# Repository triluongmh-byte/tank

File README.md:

# Pet Tank 🛞🤖

**English** · [Tiếng Việt](README.vi.md)

A 6-wheel armored-car-style tank cloned from **claude-pet**. A screen on the sloped front face shows the pet face and the status of Claude Code sessions. A turret carries two sonars mounted back to back for finding a path.

- **Body:** the `robot-tank` v1 case designed in cadsmith, already printed by the owner, plus the v5 board stack and glue-on/clip-on holders.
- **Board:** 62×60 mm two-layer carrier.
- **Control:** ESP32 DevKit + PCA9685 driving 7 servos: six 360° wheel servos and one SG90 turret servo.
- **Power:** two 18650 cells in parallel (1S) through a pack protector and two 5 V boost modules.

> **Status:** the design passed the team's board, firmware, case and integration checks. **Hardware is untested.** The firmware has not been flashed, the new holders have not been printed, and no board has been ordered. Module dimensions in the docs are **ASSUMPTIONS**: measure the real modules before printing or soldering.

## What's in the repo

| Folder | Contents |
|---|---|
| `design/` | KiCad project: schematic, PCB, libraries, component 3D models |
| `engineering/` | Power ([POWER_SYSTEM.md](engineering/POWER_SYSTEM.md)), stack wiring ([STACK_WIRING.md](engineering/STACK_WIRING.md)), assembly, bring-up, pinout, calculations |
| `parts.json`, `product.json`, `manufacturing.json` | BOM (LCSC part numbers), board description, fabrication settings |
| `case/` | CadQuery scripts for the holders ([build.py](case/build.py), `holders.py`, `stack.py`, `power_b.py`, `logic_b.py`). `case/ref/v1` and `case/ref/v5` hold the original STEP files of the printed robot-tank, unchanged |
| `firmware/` | ESP32 firmware (`firmware/tank/`), [wiring guide](firmware/WIRING.md), [host protocol](firmware/PROTOCOL.md), host-side tests (`firmware/tests/`), host bridge (`firmware/host/`) |
| `tools/` | Check and export scripts for each team (board, case, firmware) |
| `contract/` | The sealed team contract and release notes (the owner's words verbatim, plus how the lead interpreted them) |
| `prompts/`, `references/` | Original request, request history, reference images. STEP/STL files under `prompts/assets` are not committed; their hashes are in the `SHA256SUMS` files |

Not committed, because `./build.sh` regenerates them: STL/STEP/3MF, Gerbers, zips, renders, `build/`, `boards/`, `case/out/`, `case/print/`, firmware binaries. Datasheets are not committed either; their links are in `engineering/sources/manifest.json`.

Most docs inside the subfolders are written in Vietnamese.

## Build

```sh
./build.sh              # board -> case -> firmware
./build.sh firmware     # a single stage
./build.sh board case
```

Requirements (nothing is installed from the network):

- `KICAD_HARNESS_PYTHON` (Python with `kicadpy`) and `KICAD_CASE_PYTHON` (Python with CadQuery + `kicadpy`). Harness provides both.
- KiCad 9 `kicad-cli`. The script looks in `/Applications/KiCad/KiCad.app`, or set `KICAD_CLI`.
- Bambu Studio at `/Applications/BambuStudio.app`, used to slice `case/print/*.3mf`. No print job is ever sent.
- `arduino-cli` with core `esp32:esp32@2.0.14` already installed. If the core is outside the default location, point `ARDUINO_DIRECTORIES_DATA` at it (Harness keeps it in `~/.cache/autonomous-circuit/firmware/arduino`).

A build rewrites a few committed files: the board STEP hashes in `case/ref/board/SHA256SUMS`, `engineering/step-handoff.json` and `case/firmware-limits.json`. Seeing them change after a build is expected.

What each stage does:

- **board:** runs the official board checks (ERC/DRC, netlist, gate) and writes the manufacturing packet to `boards/`. Exports the populated board STEP to `build/board/main-contract.step` and hands it to the case (`case/ref/board/`, hashes recomputed).
- **case:** runs `case/build.py`, which writes STEP/STL to `case/out/`. Then runs the three case checks: printability and collisions, v5 against v1, and turret sweep. Then generates the print plates `case/print/production.3mf` + `test-only.3mf` and `case/overview.html`, and runs `kicadpy.case check-print` (printable surfaces, bed fit).
- **firmware:** runs the host tests, including mocks and ASan/UBSan, then compiles the ESP32 build to `build/firmware/esp32/tank.ino.bin`. **Nothing is flashed.**

When a requested stage reads another stage's output and that output is missing, `build.sh` runs that stage too. The case needs the board STEP. The firmware needs `case/reports/turret_yaw.json` for the turret limits.

## What the firmware does

- Keeps claude-pet's pet face and Claude Code session status, now on a 1.54" 240×240 ST7789 screen.
- Talks to a computer over USB (UART0, 115200).
- **Phone control**, modelled on the UI of the owner's crab-robot-v17g:
  - The tank starts its own open Wi-Fi network named `XeTang-XXXX`. The screen shows the network name, the address and a QR code.
  - Join that network and open `http://192.168.4.1/`. Many phones open the page on their own.
  - **Drive** page: an 8-direction pad. Hold a button to drive, release to stop. Three speeds: 0.4 / 0.65 / 1. Forward or reverse is blocked when the sonar facing that way sees an obstacle closer than 350 mm, or has no fresh reading (older than 250 ms). The light button shows "not connected" because the lights have no control pin yet.
  - **Assembly** page: set the centre, limits and direction for each wheel, centre the turret (limited to ±70°), then Save. Driving is refused until calibration is done.
  - **Wi-Fi** page (optional): join a home network. The password is stored in NVS.
  - Every stop source wins: releasing the button, no command for 500 ms, losing the phone connection, the STOP button, an I2C error, the watchdog.
  - The constants (500 ms, 5 s, 60 % pulse at speed 1) are **untested** on the real tank and a real phone.
- The board adds a logic boost module, `M_LOGIC` (Pololu U3V16F5), that powers the DevKit over USB from the battery. The tank can run without a computer attached.
- Drives the six wheels (PCA CH0–5) with per-wheel calibration, and the turret (CH6).
- A stop-and-go path-finding mode using the two HC-SR04P sonars. `AUTO SCAN` stays locked until the real turret angles are measured on the tank.
- Always boots stopped. Losing the link, a missed heartbeat, or the STOP button (GPIO27) cuts servo power.

GPIO map: see [firmware/README.md](firmware/README.md) and [engineering/esp32-pinmap.json](engineering/esp32-pinmap.json).

## Case: what to print and how to assemble

See [case/README.md](case/README.md). In short:

- **Do not reprint** the robot-tank v1 parts that are already printed: chassis, hull, lid, turret, light bracket, six arms, six wheels.
- Print the new glue-on/clip-on holders and the **v5 stack**: base, PCA9685 + fan tier, ESP32 tier, and a cap with a turret-servo pocket and a 45° face for the screen.
- **Layout B** is the chosen layout: the lid is removed and the stack stands on a bridge plate above the two cells. Total height is **214.8 mm**, against 118.3 mm for v1. Only layout B fits the 62×60 carrier with all the modules.
- Print the **TEST ONLY** plate first and try it with the real modules before printing the production plates.

## Things you may need to fix by hand

The testers recorded the points below. Items 1–8 come from run `r006` and may be partly fixed. Items 9–11 come from the latest run, `r007`. Neither run produced a `lead-document-findings.json`. None of these have been measured on hardware.

1. **The servo boost converters are near their limit.** The estimated peak current drawn from the battery is ~8.9 A, above the 8 A typical rating of the Pololu U3V70F5. Measure the real current with all six wheels stalled or starting, and consider limiting speed or splitting the load.
2. **The power docs still contain old text.** Some lines in `product.json`, `engineering/POWER_SYSTEM.md` and `parts.json` still describe the old power chain (TPS61287, LILYGO, 100×70 carrier, 12 AWG / 30 A wiring). The current design uses two Pololu U3V70F5 modules, an ESP32 DevKit and a 62×60 carrier. The main battery lead needs connectors rated ≥15 A to match the `F_PACK` fuse.
3. **ACT_EN while the ESP32 boots.** The second boost module's ENABLE pin is tied to ACT_EN through a Dupont lead and pulled up to VIN (≤4.2 V) through 100 kΩ. Check on the bench that ACT_EN stays low while the ESP32 boots and resets, so the servos don't twitch.
4. **The 2×6 header orientation in `firmware/WIRING.md`** does not match the new 62×60 layout. Use [engineering/pinout.md](engineering/pinout.md) when crimping the `J_CTRL` / `J_PCA` leads.
5. **The unfused battery lead is ~35 mm long**, over the ≤25 mm limit. Move the `fuse_holder_pack` holder closer to the cells, or fit `F_PACK` inside the battery pack.
6. **There is no place for the charger on the tank.** To charge, unplug the RUN connector and charge on the bench.
7. **Module dimensions are assumed:** ESP32 51.5×28.3, PCA9685 62.2×25.4, fan 30×30×10, screen 32×38×4 mm. Measure the real parts and print the TEST ONLY coupons first.
8. **Layout B makes the tank almost twice as tall** and drops the lid. Keeping the v1 lid needs a redesign by the team.
9. **The power diagrams don't show `M_LOGIC` yet.** Parts of `engineering/POWER_SYSTEM.md` still say the DevKit takes 5 V from its own USB supply, and one line still mentions the LILYGO. `case/logic_b.py` and the firmware integration report still refer to the old "optional chain". The bring-up order in `firmware/WIRING.md` (logic first, then islands A/B) does not match the diagram, where all three boost modules are wired in parallel at the RUN lead.
10. **Where the DevKit sits:** the `M_LOGIC` wire route says the DevKit is on "tier 3", while `STACK_WIRING.md` and `parts.json` put it on tier 2. Tier 2 is correct.
11. **Power the DevKit through its USB port only.** Do not also feed its VIN pin in parallel with USB.

## Safety

A 1S Li-ion pack delivers high current. Fit the protector and fuses described in [engineering/POWER_SYSTEM.md](engineering/POWER_SYSTEM.md). Never connect the outputs of the two boost modules in parallel. Never power the servos from the DevKit's 5V pin or from a computer's USB port.

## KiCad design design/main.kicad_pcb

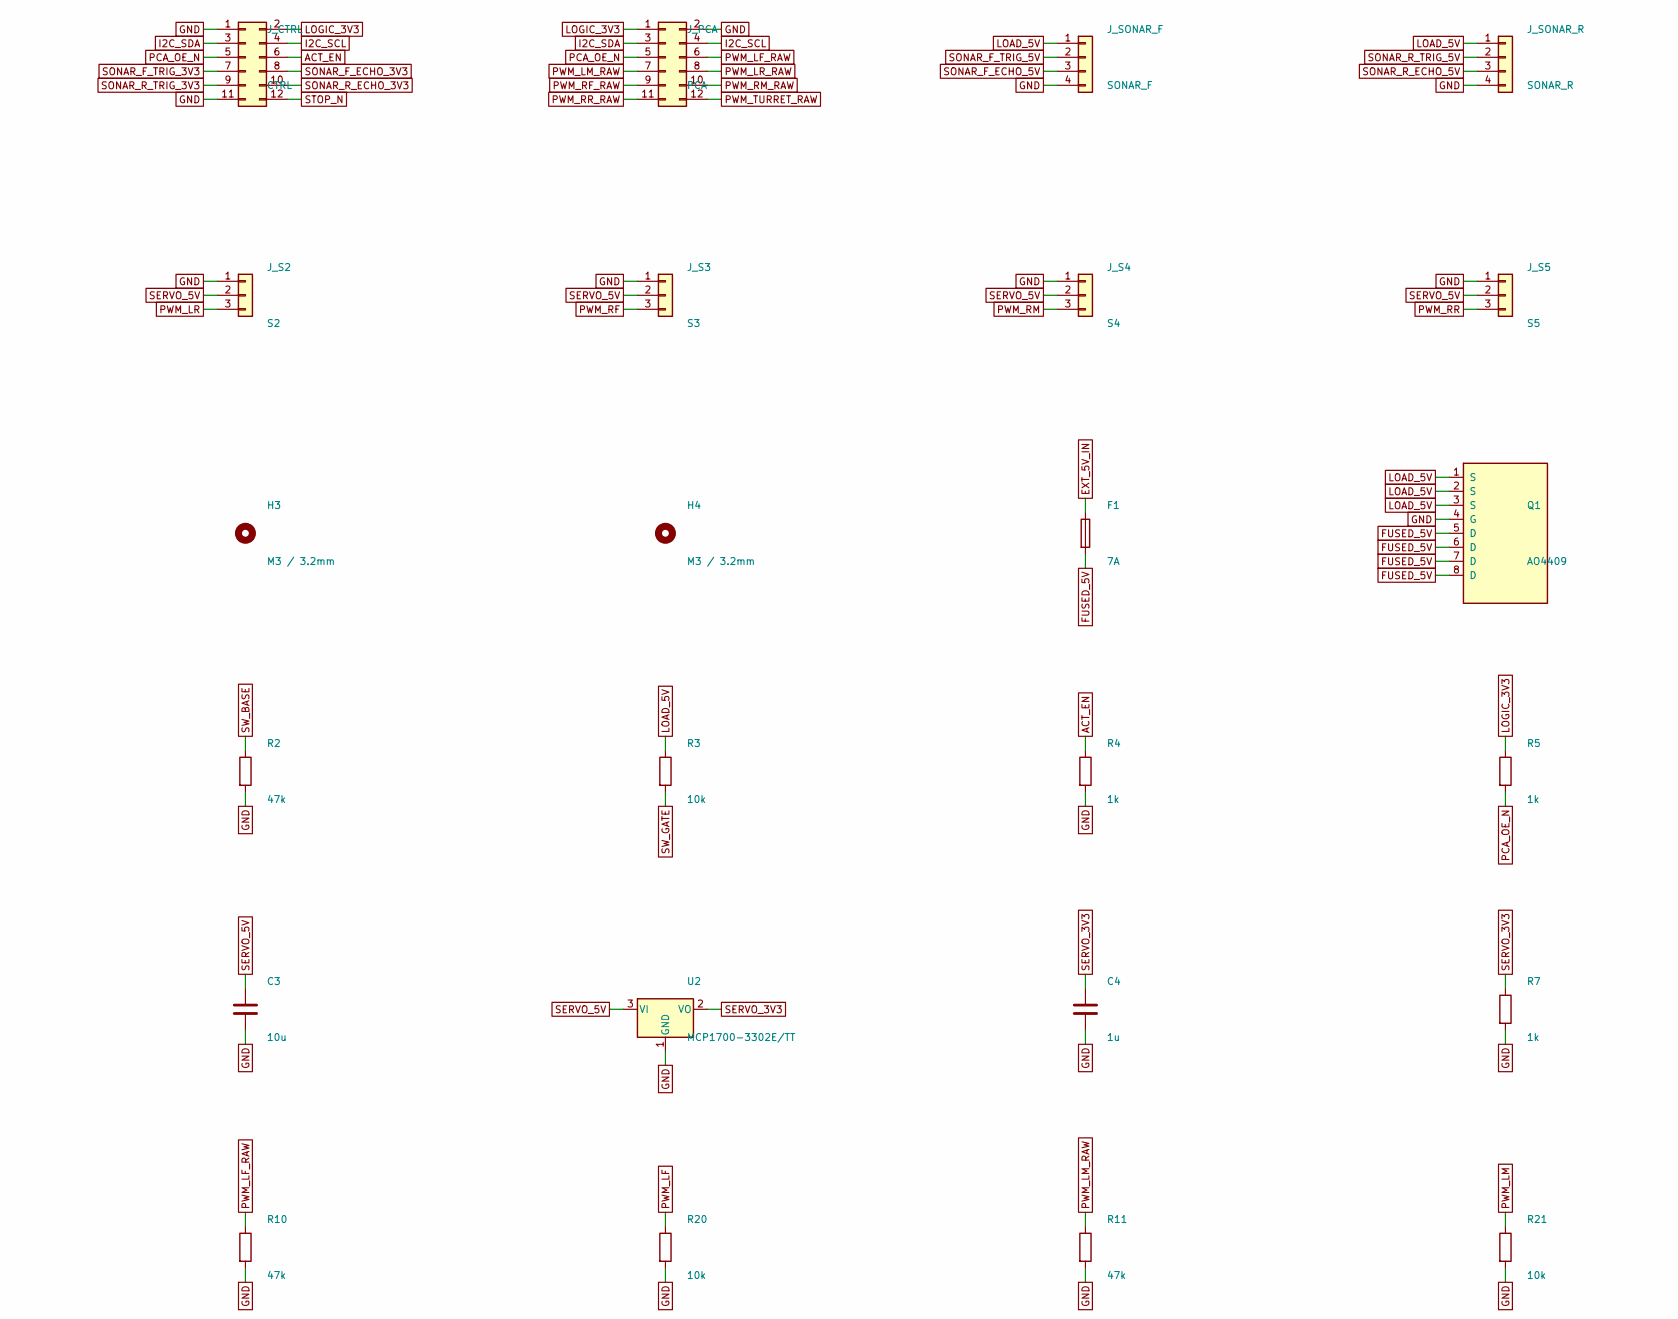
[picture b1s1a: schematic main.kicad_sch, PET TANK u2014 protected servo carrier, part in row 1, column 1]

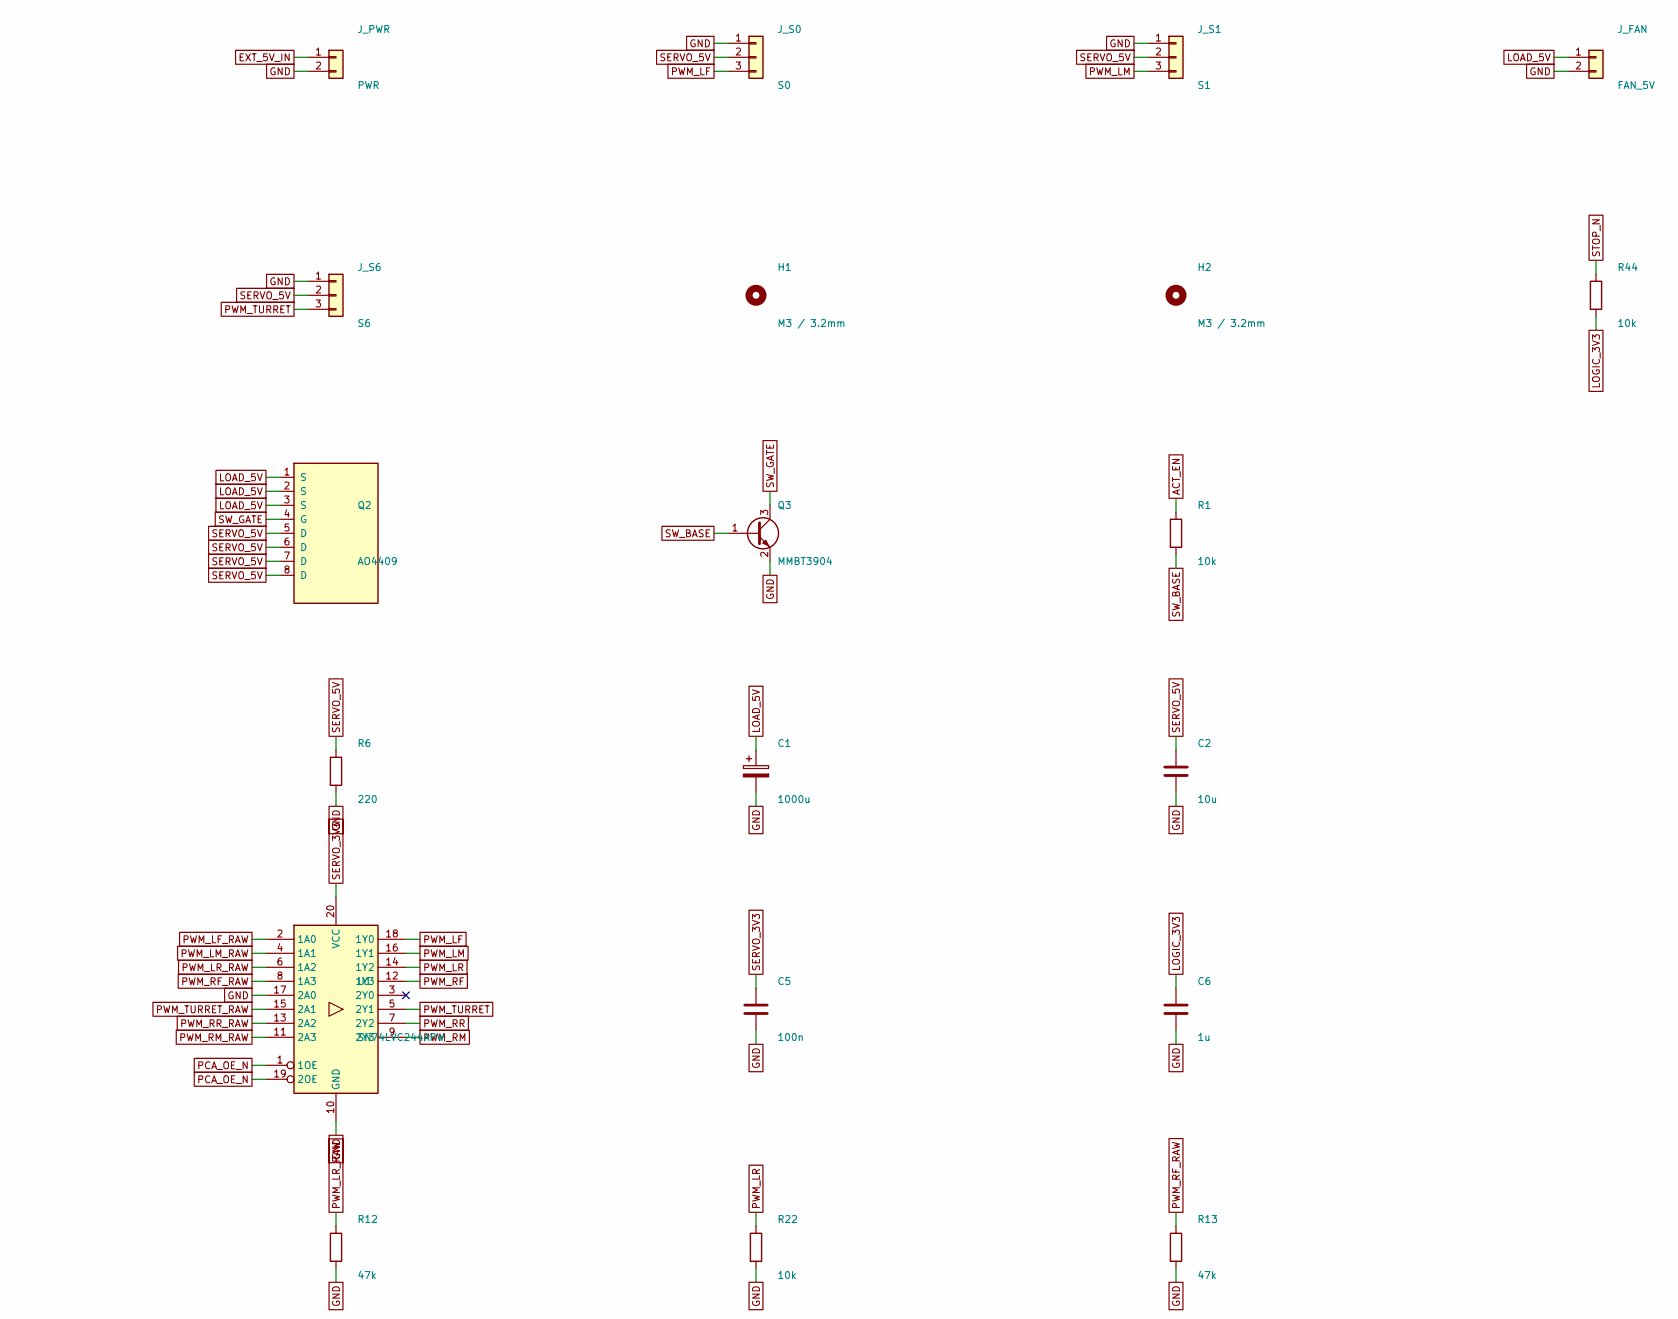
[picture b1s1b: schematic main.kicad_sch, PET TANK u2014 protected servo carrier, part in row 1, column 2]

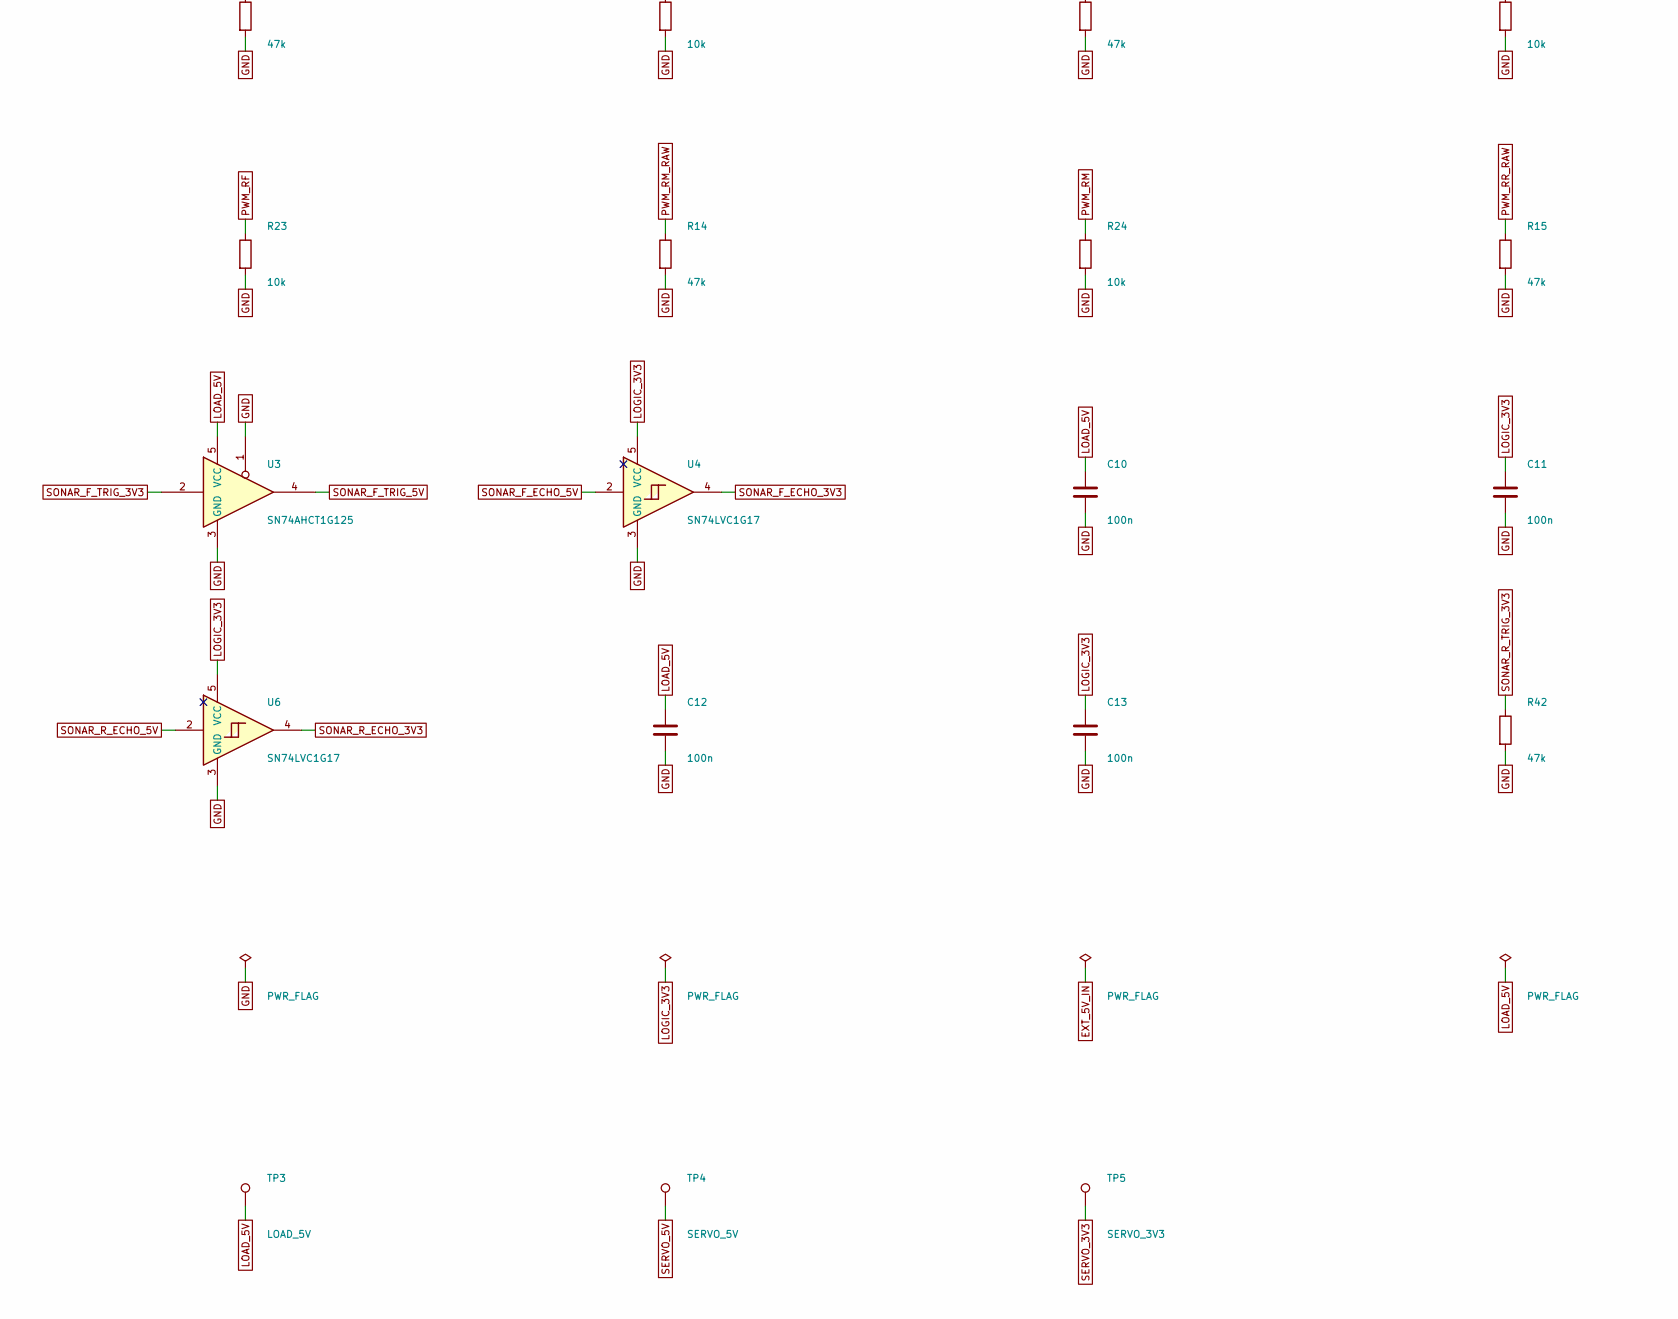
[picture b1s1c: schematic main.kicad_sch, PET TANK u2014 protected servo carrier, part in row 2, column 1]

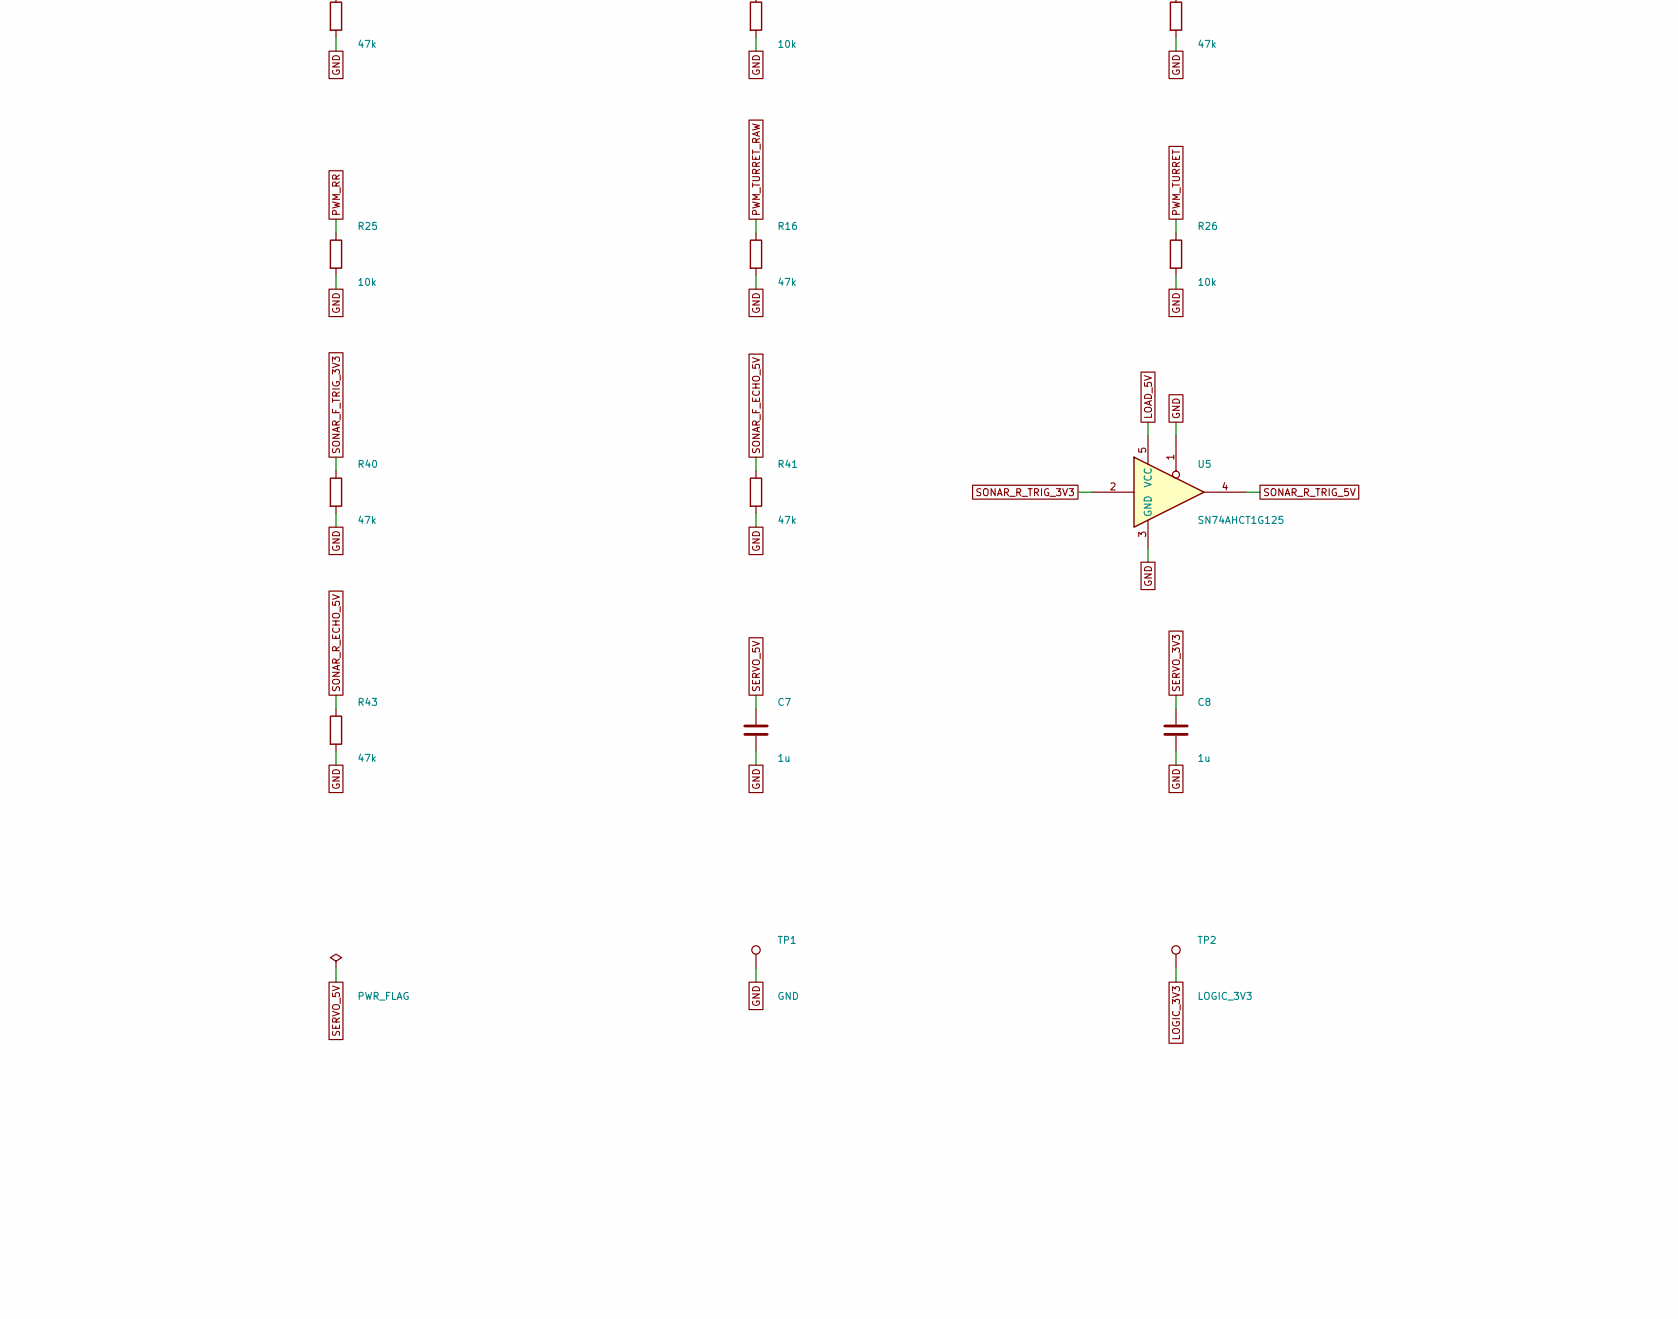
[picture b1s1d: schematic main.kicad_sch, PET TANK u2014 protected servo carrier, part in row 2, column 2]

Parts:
C1: 1000u; CP_Radial_D10.0mm_P5.00mm
C2, C3: 10u; C_0805_2012Metric
C4, C6, C7, C8: 1u; C_0805_2012Metric
C5, C10, C11, C12, C13: 100n; C_0805_2012Metric
F1: 7A; Fuse_2512_6332Metric
H1, H2, H3, H4: M3 / 3.2mm; MountingHole_3.2mm_M3
J_CTRL: CTRL; PinHeader_2x06_P2.54mm_Vertical
J_FAN: FAN_5V; TerminalBlock_Phoenix_MKDS-1,5-2-5.08_1x02_P5.08mm_Horizont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
J_PCA: PCA; PinHeader_2x06_P2.54mm_Vertical
J_PWR: PWR; TerminalBlock_Phoenix_MKDS-1,5-2-5.08_1x02_P5.08mm_Horizont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
J_S0: S0; PinHeader_1x03_P2.54mm_Vertical
J_S1: S1; PinHeader_1x03_P2.54mm_Vertical
J_S2: S2; PinHeader_1x03_P2.54mm_Vertical
J_S3: S3; PinHeader_1x03_P2.54mm_Vertical
J_S4: S4; PinHeader_1x03_P2.54mm_Vertical
J_S5: S5; PinHeader_1x03_P2.54mm_Vertical
J_S6: S6; PinHeader_1x03_P2.54mm_Vertical
J_SONAR_F: SONAR_F; PinHeader_1x04_P2.54mm_Vertical
J_SONAR_R: SONAR_R; PinHeader_1x04_P2.54mm_Vertical
Q1, Q2: AO4409; SOIC-8_3.9x4.9mm_P1.27mm
Q3: MMBT3904; SOT-23
R1, R3, R20, R21, R22, R23, R24, R25, R26, R44: 10k; R_0805_2012Metric
R2, R10, R11, R12, R13, R14, R15, R16, R40, R41, R42, R43: 47k; R_0805_2012Metric
R4, R5, R7: 1k; R_0805_2012Metric
R6: 220; R_2512_6332Metric
TP1: GND; TestPoint_Pad_D2.0mm
TP2: LOGIC_3V3; TestPoint_Pad_D2.0mm
TP3: LOAD_5V; TestPoint_Pad_D2.0mm
TP4: SERVO_5V; TestPoint_Pad_D2.0mm
TP5: SERVO_3V3; TestPoint_Pad_D2.0mm
U1: SN74LVC244APW; TSSOP-20_4.4x6.5mm_P0.65mm
U2: MCP1700-3302E/TT; SOT-23
U3, U5: SN74AHCT1G125; SOT-23-5
U4, U6: SN74LVC1G17; SOT-23-5

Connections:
ACT_EN: J_CTRL.6, R1.1, R4.1
EXT_5V_IN: F1.1, J_PWR.1
FUSED_5V: F1.2, Q1.5 (D), Q1.6 (D), Q1.7 (D), Q1.8 (D)
GND: C1.2, C2.2, C3.2, C4.2, C5.2, C6.2, C7.2, C8.2, C10.2, C11.2, C12.2, C13.2, J_CTRL.1, J_CTRL.11, J_FAN.2, J_PCA.2, J_PWR.2, J_S0.1, J_S1.1, J_S2.1, J_S3.1, J_S4.1, J_S5.1, J_S6.1, J_SONAR_F.4, J_SONAR_R.4, Q1.4 (G), Q3.2 (E), R2.2, R4.2, R6.2, R7.2, R10.2, R11.2, R12.2, R13.2, R14.2, R15.2, R16.2, R20.2, R21.2, R22.2, R23.2, R24.2, R25.2, R26.2, R40.2, R41.2, R42.2, R43.2, TP1.1, U1.10 (GND), U1.17 (2A0), U2.1 (GND), U3.1, U3.3 (GND), U4.3 (GND), U5.1, U5.3 (GND), U6.3 (GND)
I2C_SCL: J_CTRL.4, J_PCA.4
I2C_SDA: J_CTRL.3, J_PCA.3
LOAD_5V: C1.1, C10.1, C12.1, J_FAN.1, J_SONAR_F.1, J_SONAR_R.1, Q1.1 (S), Q1.2 (S), Q1.3 (S), Q2.1 (S), Q2.2 (S), Q2.3 (S), R3.1, TP3.1, U3.5 (VCC), U5.5 (VCC)
LOGIC_3V3: C6.1, C11.1, C13.1, J_CTRL.2, J_PCA.1, R5.1, R44.2, TP2.1, U4.5 (VCC), U6.5 (VCC)
PCA_OE_N: J_CTRL.5, J_PCA.5, R5.2, U1.1 (1OE), U1.19 (2OE)
PWM_LF: J_S0.3, R20.1, U1.18 (1Y0)
PWM_LF_RAW: J_PCA.6, R10.1, U1.2 (1A0)
PWM_LM: J_S1.3, R21.1, U1.16 (1Y1)
PWM_LM_RAW: J_PCA.7, R11.1, U1.4 (1A1)
PWM_LR: J_S2.3, R22.1, U1.14 (1Y2)
PWM_LR_RAW: J_PCA.8, R12.1, U1.6 (1A2)
PWM_RF: J_S3.3, R23.1, U1.12 (1Y3)
PWM_RF_RAW: J_PCA.9, R13.1, U1.8 (1A3)
PWM_RM: J_S4.3, R24.1, U1.9 (2Y3)
PWM_RM_RAW: J_PCA.10, R14.1, U1.11 (2A3)
PWM_RR: J_S5.3, R25.1, U1.7 (2Y2)
PWM_RR_RAW: J_PCA.11, R15.1, U1.13 (2A2)
PWM_TURRET: J_S6.3, R26.1, U1.5 (2Y1)
PWM_TURRET_RAW: J_PCA.12, R16.1, U1.15 (2A1)
SERVO_3V3: C4.1, C5.1, C8.1, R7.1, TP5.1, U1.20 (VCC), U2.2 (VO)
SERVO_5V: C2.1, C3.1, C7.1, J_S0.2, J_S1.2, J_S2.2, J_S3.2, J_S4.2, J_S5.2, J_S6.2, Q2.5 (D), Q2.6 (D), Q2.7 (D), Q2.8 (D), R6.1, TP4.1, U2.3 (VI)
SONAR_F_ECHO_3V3: J_CTRL.8, U4.4
SONAR_F_ECHO_5V: J_SONAR_F.3, R41.1, U4.2
SONAR_F_TRIG_3V3: J_CTRL.7, R40.1, U3.2
SONAR_F_TRIG_5V: J_SONAR_F.2, U3.4
SONAR_R_ECHO_3V3: J_CTRL.10, U6.4
SONAR_R_ECHO_5V: J_SONAR_R.3, R43.1, U6.2
SONAR_R_TRIG_3V3: J_CTRL.9, R42.1, U5.2
SONAR_R_TRIG_5V: J_SONAR_R.2, U5.4
STOP_N: J_CTRL.12, R44.1
SW_BASE: Q3.1 (B), R1.2, R2.1
SW_GATE: Q2.4 (G), Q3.3 (C), R3.2

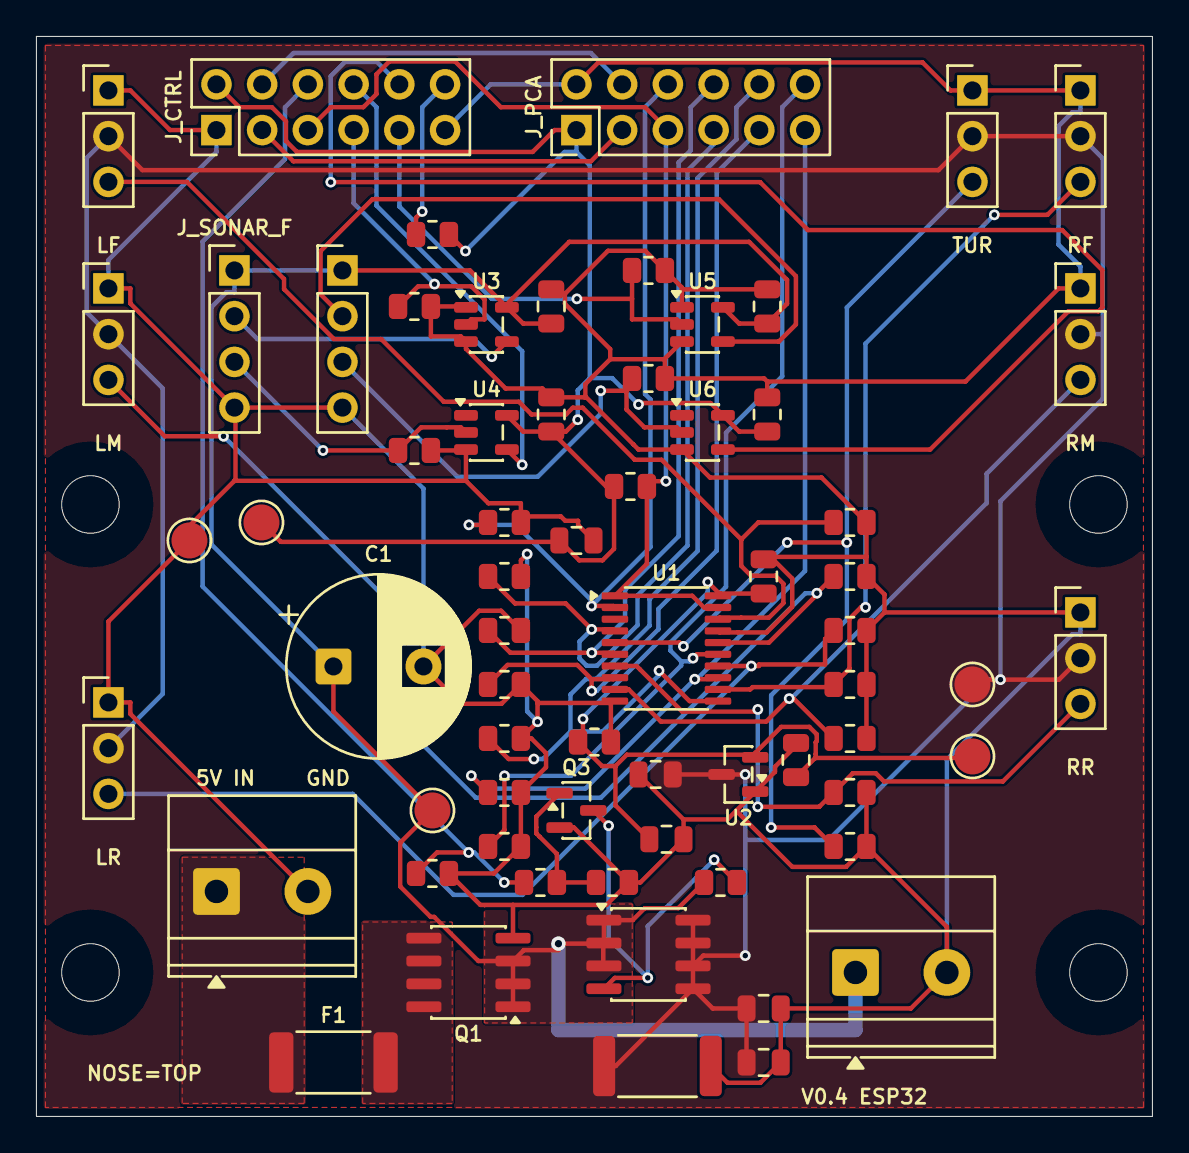
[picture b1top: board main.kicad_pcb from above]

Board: 2 copper layers, 62.0 x 60.0 mm, 70 parts (0 on the bottom side), 36 nets.

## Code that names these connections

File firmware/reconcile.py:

#!/usr/bin/env python3
"""Read-only contract/PCB/case reconciliation; reports only inside firmware/."""
import argparse,hashlib,json,pathlib,re,sys
ROOT=pathlib.Path(__file__).resolve().parent.parent
FIRM=ROOT/'firmware'
SHA='a3ef67fc11d668fdbe01fd2d5a06c6fef5fed069868d7fb6fb4b3995edd55810'
def sha(p):return hashlib.sha256(p.read_bytes()).hexdigest()
def sexpr(text):
 tokens=re.findall(r'"(?:\\.|[^"\\])*"|[()]|[^\s()]+',text);stack=[];root=[];current=root
 for token in tokens:
  if token=='(':child=[];current.append(child);stack.append(current);current=child
  elif token==')':current=stack.pop()
  else:current.append(json.loads(token) if token.startswith('"') else token)
 if stack:raise ValueError('Unbalanced PCB expression')
 return root[0]
def tagged(node,tag):return [x for x in node if isinstance(x,list) and x and x[0]==tag]
def measure(pcb):
 root=sexpr(pcb.read_text());nets={x[1]:x[2] for x in tagged(root,'net') if len(x)>2};out={}
 for footprint in tagged(root,'footprint'):
  refs=[x[2] for x in tagged(footprint,'property') if x[1]=='Reference']+[x[2] for x in tagged(footprint,'fp_text') if x[1]=='reference']
  if not refs:continue
  ref=refs[0];pads={}
  for pad in tagged(footprint,'pad'):
   padnets=tagged(pad,'net');name='NC'
   if padnets:
    net=padnets[0]
    # KiCad 10 writes (net "name"); earlier versions use (net id "name").
    name=net[2] if len(net)>2 else nets.get(net[1],net[1])
   if pad[1] in pads and pads[pad[1]]!=name:raise ValueError('Inconsistent duplicated pad '+ref+'.'+pad[1])
   pads[pad[1]]=name
  out[ref]=pads
 return out

def compare_board(measured,pins):
 """Check connector nets plus the board's documented, noninverting U1 paths."""
 errors=[];connectors={};paths=[]
 channels=('LF','LM','LR','RF','RM','RR','TURRET')
 buffer_pins=((2,18),(4,16),(6,14),(8,12),(11,9),(13,7),(15,5))
 for pin in pins:
  ref=pin['device'];pad=pin['pin'];want=pin['net']
  if not ref.startswith('J_'):continue
  got=measured.get(ref,{}).get(pad,'MISSING');connectors.setdefault(ref,{})[pad]=got
  if ref=='J_CTRL' and pad=='12' and want=='NC' and got=='STOP_N':continue  # note 8: board assigns local stop here
  if ref=='J_CTRL' and pad=='12' and want=='NC' and got=='unconnected-(J_CTRL-Pin_12-Pad12)':
   # A named unconnected net is NC only if no second pad shares it.
   if sum(n==got for pads in measured.values() for n in pads.values())==1:continue
  if ref=='J_PCA' and pad in tuple(str(i) for i in range(6,13)) and got==want+'_RAW':
   ch=int(pad)-6;input_pin,output_pin=buffer_pins[ch];u=measured.get('U1',{})
   expected='PWM_'+channels[ch]
   ok=(want==expected and u.get(str(input_pin))==got and u.get(str(output_pin))==want
       and measured.get('J_S'+str(ch),{}).get('3')==want
       and u.get('1')==u.get('19')=='PCA_OE_N' and u.get('10')=='GND' and u.get('20')=='SERVO_3V3')
   paths.append({'channel':ch,'inputPin':input_pin,'outputPin':output_pin,'inputNet':got,'outputNet':want,'ok':ok})
   if ok:continue
   errors.append(f'{ref}.{pad}: buffered path through U1 differs')
   continue
  if got!=want:errors.append(f'{ref}.{pad}: PCB {got}, contract {want}')
 # Release notes add an always-powered 5 V fan; no GPIO or servo-enable coupling.
 for pad,want in (('1','LOAD_5V'),('2','GND')):
  got=measured.get('J_FAN',{}).get(pad,'MISSING');connectors.setdefault('J_FAN',{})[pad]=got
  if got!=want:errors.append(f'J_FAN.{pad}: PCB {got}, release notes {want}')
 return errors,connectors,paths

def main():
 parser=argparse.ArgumentParser();parser.add_argument('--require-board',action='store_true');parser.add_argument('--require-case',action='store_true');args=parser.parse_args()
 contract=ROOT/'PILOT_CONTRACT.json';data=json.loads(contract.read_text());pins=data['interfaces']['pins']
 report={'schema':1,'contractSha256':SHA,'contractFileSha256':sha(contract),'hardwareTested':False,'mismatches':[],'board':'pending','case':'pending'}
 if sha(contract)!=SHA:report['mismatches'].append('sealed contract SHA differs')
 definitions=(FIRM/'tank/pins.h').read_text()
 constants={k:int(v) for k,v in re.findall(r'\b([A-Z][A-Z_]+)\s*=\s*(\d+)',definitions)}
 mapping={'I2C_SDA':constants['SDA_PIN'],'I2C_SCL':constants['SCL_PIN'],'PCA_OE_N':constants['OE_PIN'],'ACT_EN':constants['ACT_PIN']}
 arrays={k:[int(x) for x in v.split(',')] for k,v in re.findall(r'(TRIG_PINS|ECHO_PINS)\[2\]=\{([^}]+)\}',definitions)}
 mapping.update({'SONAR_F_TRIG_3V3':arrays['TRIG_PINS'][0],'SONAR_R_TRIG_3V3':arrays['TRIG_PINS'][1],'SONAR_F_ECHO_3V3':arrays['ECHO_PINS'][0],'SONAR_R_ECHO_3V3':arrays['ECHO_PINS'][1]})
 for pin in pins:
  pass  # sealed LILYGO GPIO names no longer bind firmware (release note 8); the board's DevKit map below does.
 pm=ROOT/'engineering/esp32-pinmap.json'
 if pm.exists():
  table=json.loads(pm.read_text());report['mcuPins']='compared with engineering/esp32-pinmap.json';report['pinmapSha256']=sha(pm)
  want={'I2C_SDA':constants['SDA_PIN'],'I2C_SCL':constants['SCL_PIN'],'PCA_OE_N':constants['OE_PIN'],'ACT_EN':constants['ACT_PIN'],'STOP_N':constants['STOP_PIN']}
  want.update({k:v for k,v in mapping.items() if k.startswith('SONAR')})
  seen=set()
  for row in table['carrierHarness']:
   net=row['net']
   if net in want:
    m=re.search(r'GPIO(\d+)',row['esp32']);seen.add(net)
    if not m or int(m[1])!=want[net]:report['mismatches'].append(f"{net}: firmware GPIO{want[net]}, board {row['esp32']}")
  for net in want:
   if net not in seen:report['mismatches'].append('board pin map lacks '+net)
  for sig,gpio in (('SCK',constants['LCD_SCK']),('MOSI',constants['LCD_MOSI']),('CS',constants['LCD_CS']),('DC',constants['LCD_DC']),('RST',constants['LCD_RST']),('BL',constants['LCD_BL'])):
   rows=[r for r in table['displayST7789_1p54_240x240_SPI_direct_wires_not_on_carrier'] if r['signal'].startswith(sig) or sig in r['signal'].split('/')]
   if not rows or not re.search(r'GPIO'+str(gpio)+r'\b',rows[0]['esp32']):report['mismatches'].append('display '+sig+' differs from board map')
 else:
  report['mcuPins']='board pin map absent';report['mismatches'].append('engineering/esp32-pinmap.json missing')
 pcb=ROOT/'design/main.kicad_pcb'
 if pcb.exists():
  measured=measure(pcb);report['board']='checked';report['boardSha256']=sha(pcb)
  errors,connectors,paths=compare_board(measured,pins)
  report['mismatches'].extend(errors);report['measuredConnectors']=connectors;report['bufferedPaths']=paths
  report['boardScope']='electrical connector pad nets only; geometry deviations remain a lead/case integration action'
 elif args.require_board:report['mismatches'].append('native PCB unavailable')
 # The case team may supply this deliberately small, hash-bound interchange file.
 # No firmware limit is silently inferred from an overview or an unchecked geometric box.
 limits=ROOT/'case/firmware-limits.json'
 if limits.exists():
  c=json.loads(limits.read_text());report['case']='checked';report['caseLimitsSha256']=sha(limits)
  lo=c.get('turretYawMinDeg');hi=c.get('turretYawMaxDeg');sources=c.get('checkedFiles',{})
  if c.get('contractSha256')!=SHA or c.get('status')!='passed' or not sources:report['mismatches'].append('case limits lack passed hash-bound contract evidence')
  for path,digest in sources.items():
   source=(ROOT/path).resolve()
   if not source.is_relative_to(ROOT/'case') or not source.is_file() or sha(source)!=digest:report['mismatches'].append('case source hash '+path)
  if not isinstance(lo,(int,float)) or not isinstance(hi,(int,float)) or not -70<=lo<=0<=hi<=70:report['mismatches'].append('case yaw interval invalid')
  header=(FIRM/'tank/mechanical_limits.h').read_text();m=re.search(r'CASE_YAW_MIN=(-?\d+), CASE_YAW_MAX=(-?\d+)',header)
  if not m or lo!=int(m[1]) or hi!=int(m[2]):report['mismatches'].append('firmware yaw limits differ; import reviewed range into mechanical_limits.h')
 elif args.require_case:report['mismatches'].append('checked case limits unavailable')
 report['status']='failed' if report['mismatches'] else 'pending-integration' if 'pending' in (report['board'],report['case']) else 'passed'
 target=FIRM/'reports';target.mkdir(exist_ok=True);(target/'integration.json').write_text(json.dumps(report,ensure_ascii=False,indent=2)+'\n')
 print(json.dumps(report,ensure_ascii=False,indent=2));return bool(report['mismatches'])
if __name__=='__main__':sys.exit(main())

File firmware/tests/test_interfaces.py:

import importlib.util,pathlib,tempfile,unittest
root=pathlib.Path(__file__).resolve().parents[2]
spec=importlib.util.spec_from_file_location('reconcile',root/'firmware/reconcile.py');m=importlib.util.module_from_spec(spec);spec.loader.exec_module(m)
class TestPcbMeasurement(unittest.TestCase):
 def test_measures_connector_pad_nets(self):
  text='''(kicad_pcb (version 20241229) (net 1 "GND") (net 2 "I2C_SDA")
  (footprint "Local:Header" (property "Reference" "J_CTRL")
   (pad "1" thru_hole rect (at 0 0) (net 1 "GND"))
   (pad "3" thru_hole circle (at 2.54 0) (net 2 "I2C_SDA"))
   (pad "12" thru_hole circle (at 5.08 0))))'''
  path=root/'build/firmware/tests/mock-main.kicad_pcb';path.parent.mkdir(parents=True,exist_ok=True);path.write_text(text)
  measured=m.measure(path);self.assertEqual(measured['J_CTRL'],{'1':'GND','3':'I2C_SDA','12':'NC'})
 def test_duplicate_pad_mismatch_fails(self):
  path=root/'build/firmware/tests/mock-duplicate.kicad_pcb';path.write_text('(kicad_pcb (footprint "X" (property "Reference" "J_CTRL") (pad "1" thru_hole rect (net 1 "GND")) (pad "1" thru_hole rect (net 2 "5V"))))')
  with self.assertRaises(ValueError):m.measure(path)
 def test_kicad10_name_only_nets(self):
  path=root/'build/firmware/tests/mock-kicad10.kicad_pcb'
  path.write_text('(kicad_pcb (version 20260206) (footprint "X" (property "Reference" "J_FAN") (pad "1" thru_hole rect (net "LOAD_5V")) (pad "2" thru_hole circle (net "GND"))))')
  self.assertEqual(m.measure(path),{'J_FAN':{'1':'LOAD_5V','2':'GND'}})
 def buffered_fixture(self):
  measured={'J_FAN':{'1':'LOAD_5V','2':'GND'},'J_PCA':{},'U1':{'1':'PCA_OE_N','19':'PCA_OE_N','10':'GND','20':'SERVO_3V3'}};pins=[]
  for ch,(name,(a,b)) in enumerate(zip(('LF','LM','LR','RF','RM','RR','TURRET'),((2,18),(4,16),(6,14),(8,12),(11,9),(13,7),(15,5)))):
   net='PWM_'+name;pad=str(ch+6);measured['J_PCA'][pad]=net+'_RAW'
   measured['U1'][str(a)]=net+'_RAW';measured['U1'][str(b)]=net;measured['J_S'+str(ch)]={'3':net}
   pins.append({'device':'J_PCA','pin':pad,'net':net})
  return measured,pins
 def test_all_buffered_paths_and_crossed_channel(self):
  measured,pins=self.buffered_fixture();errors,_,paths=m.compare_board(measured,pins)
  self.assertEqual(errors,[]);self.assertEqual(len(paths),7)
  measured['U1']['16']='PWM_LF'
  self.assertIn('J_PCA.7: buffered path through U1 differs',m.compare_board(measured,pins)[0])
 def test_buffer_disable_and_supply_must_match(self):
  for pad in ('1','19','10','20'):
   measured,pins=self.buffered_fixture();measured['U1'][pad]='WRONG'
   self.assertEqual(len(m.compare_board(measured,pins)[0]),7)
 def test_named_nc_must_be_isolated(self):
  measured,pins=self.buffered_fixture();net='unconnected-(J_CTRL-Pin_12-Pad12)'
  measured['J_CTRL']={'12':net};pins.append({'device':'J_CTRL','pin':'12','net':'NC'})
  self.assertEqual(m.compare_board(measured,pins)[0],[])
  measured['OTHER']={'1':net}
  self.assertTrue(any('J_CTRL.12' in error for error in m.compare_board(measured,pins)[0]))
 def test_fan_must_not_use_switched_servo_rail(self):
  measured,pins=self.buffered_fixture();measured['J_FAN']['1']='SERVO_5V'
  self.assertIn('J_FAN.1: PCB SERVO_5V, release notes LOAD_5V',m.compare_board(measured,pins)[0])
if __name__=='__main__':unittest.main()
